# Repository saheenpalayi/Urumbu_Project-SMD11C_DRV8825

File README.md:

# Urumbu_Project-SMD11C_DRV8825

I wanted to try out the Urumbu Project by Neil Gershenfeld, at SuperFablab Kerala, Kochi but, unfortunately, we don't have a 5V stepper driver in our inventory, so thought of creating a version of the Urumbu project with SAMD11C and DRV8825 motor driver.

## Design

## Testing

## Downloads
- [SAMD11_DRV8825_NEM17.pdf](<design files/Kicad Files/SAMD11_DRV8825_NEM17.pdf>)
- [SAMD11_DRV8825_NEM17.step](<design files/Kicad Files/SAMD11_DRV8825_NEM17.step>)
- [gerber.zip](<design files/Gerber Files/gerber.zip>)
- [Firmware](firmware/urumbu-d11c-drv8825/urumbu-d11c-drv8825.ino)

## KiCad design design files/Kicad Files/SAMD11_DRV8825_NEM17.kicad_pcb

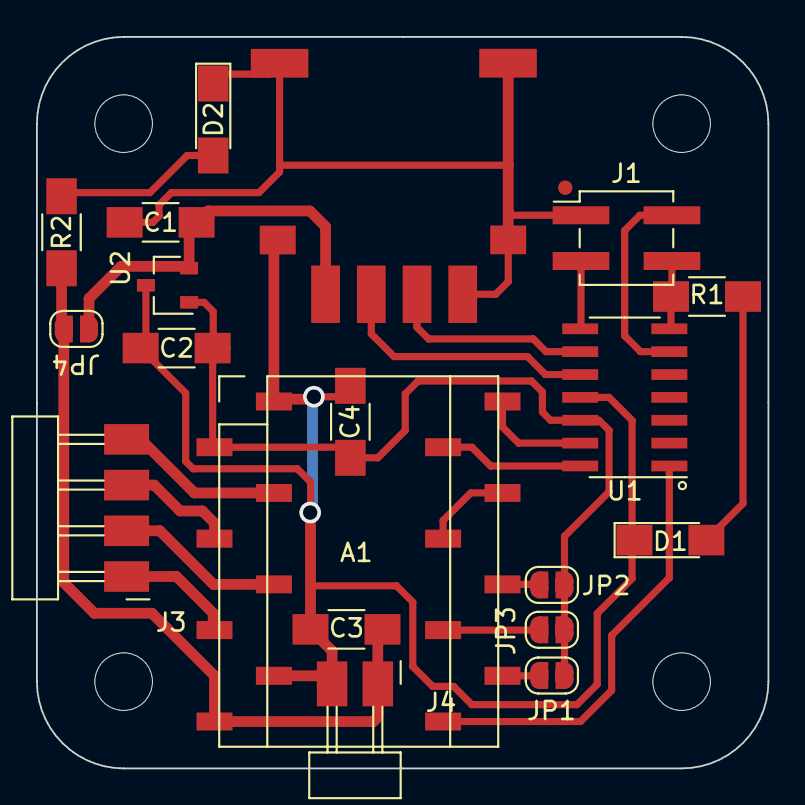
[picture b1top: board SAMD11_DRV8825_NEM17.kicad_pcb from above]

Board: 2 copper layers, 40.6 x 40.6 mm, 19 parts (0 on the bottom side), 22 nets.

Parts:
A1: Pololu_Breakout_DRV8825; DRV8825_SMD_pinheader_breakout
C1, C2, C3, C4: C_1206
D1, D2: LED_1206
J1: Conn_PinHeader_SWD_2x02_P2.54mm_Vertical_SMD; PinHeader_2x02_P2.54mm_Vertical_SMD
J2: USB_Type-C_Breakout; ProshPlay-Type-C-breakout-board
J3: Conn_PinHeader_1x04_P2.54mm_Horizontal_SMD; PinHeader_1x04_P2.54mm_Horizontal_SMD
J4: Conn_PinHeader_1x02_P2.54mm_Horizontal_SMD; PinHeader_1x02_P2.54mm_Horizontal_SMD
JP1, JP2, JP3, JP4: SolderJumper_2_Open; SolderJumper-2_P1.3mm_Open_RoundedPad1.0x1.5mm_0.4mm
R1, R2: R_1206
U1: Microcontroller_ATSAMD11C14A-SSUT; SOIC-14_3.9x8.7mm_P1.27mm
U2: Regulator_Linear_3.3V_100mA_TexasInstruments; SOT-23-3

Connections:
+3V3: A1.2 (~FLT), C2.1, C4.1, JP1.1 (A), JP2.1 (A), JP3.1 (A), U1.12 (VDD), U2.1 (VO)
+5V: C1.1, J2.1 (VBUS), JP4.1 (A), U2.2 (VI)
CLK: J1.4, R1.1, U1.7 (PA30/SWCLK)
DIO: J1.3, U1.8 (PA31/SWDIO)
DIR: A1.16 (DIR), U1.13 (PA02)
DM: J2.3 (D-), U1.9 (PA24)
DP: J2.2 (D+), U1.10 (PA25)
EN: A1.9 (~EN), U1.1 (PA05)
GND: A1.1 (GND), A1.7 (GND), C1.2, C2.2, C3.2, C4.2, D1.1 (K), D2.1 (K), J1.1, J2.4 (GND), J2.5 (Shield), J4.2, U1.11 (GND), U2.3 (GND)
M0: A1.10 (M0), JP1.2 (B)
M2: A1.12 (M2), JP2.2 (B)
M3: A1.11 (M1), JP3.2 (B)
unnamed: A1.4 (A1), J3.3
unnamed: A1.3 (A2), J3.4
unnamed: A1.5 (B1), J3.2
unnamed: A1.6 (B2), J3.1
unnamed: A1.13 (~RST), A1.14 (~SLP)
unnamed: D1.2 (A), R1.2
unnamed: D2.2 (A), R2.2
RST: J1.2, U1.6 (PA28/~RST)
STEP: A1.15 (STEP), U1.14 (PA04)
VCC: A1.8 (VMOT), C3.1, J4.1, JP4.2 (B), R2.1

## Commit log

2024-04-06 Updating files
2024-04-06 adding video
2024-04-06 test video added
